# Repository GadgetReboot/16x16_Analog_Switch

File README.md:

# I2C Controlled 16x16_Analog_Switch
<br><br><BR><BR>
MT8816 based 16x16 Analog Switch Matrix

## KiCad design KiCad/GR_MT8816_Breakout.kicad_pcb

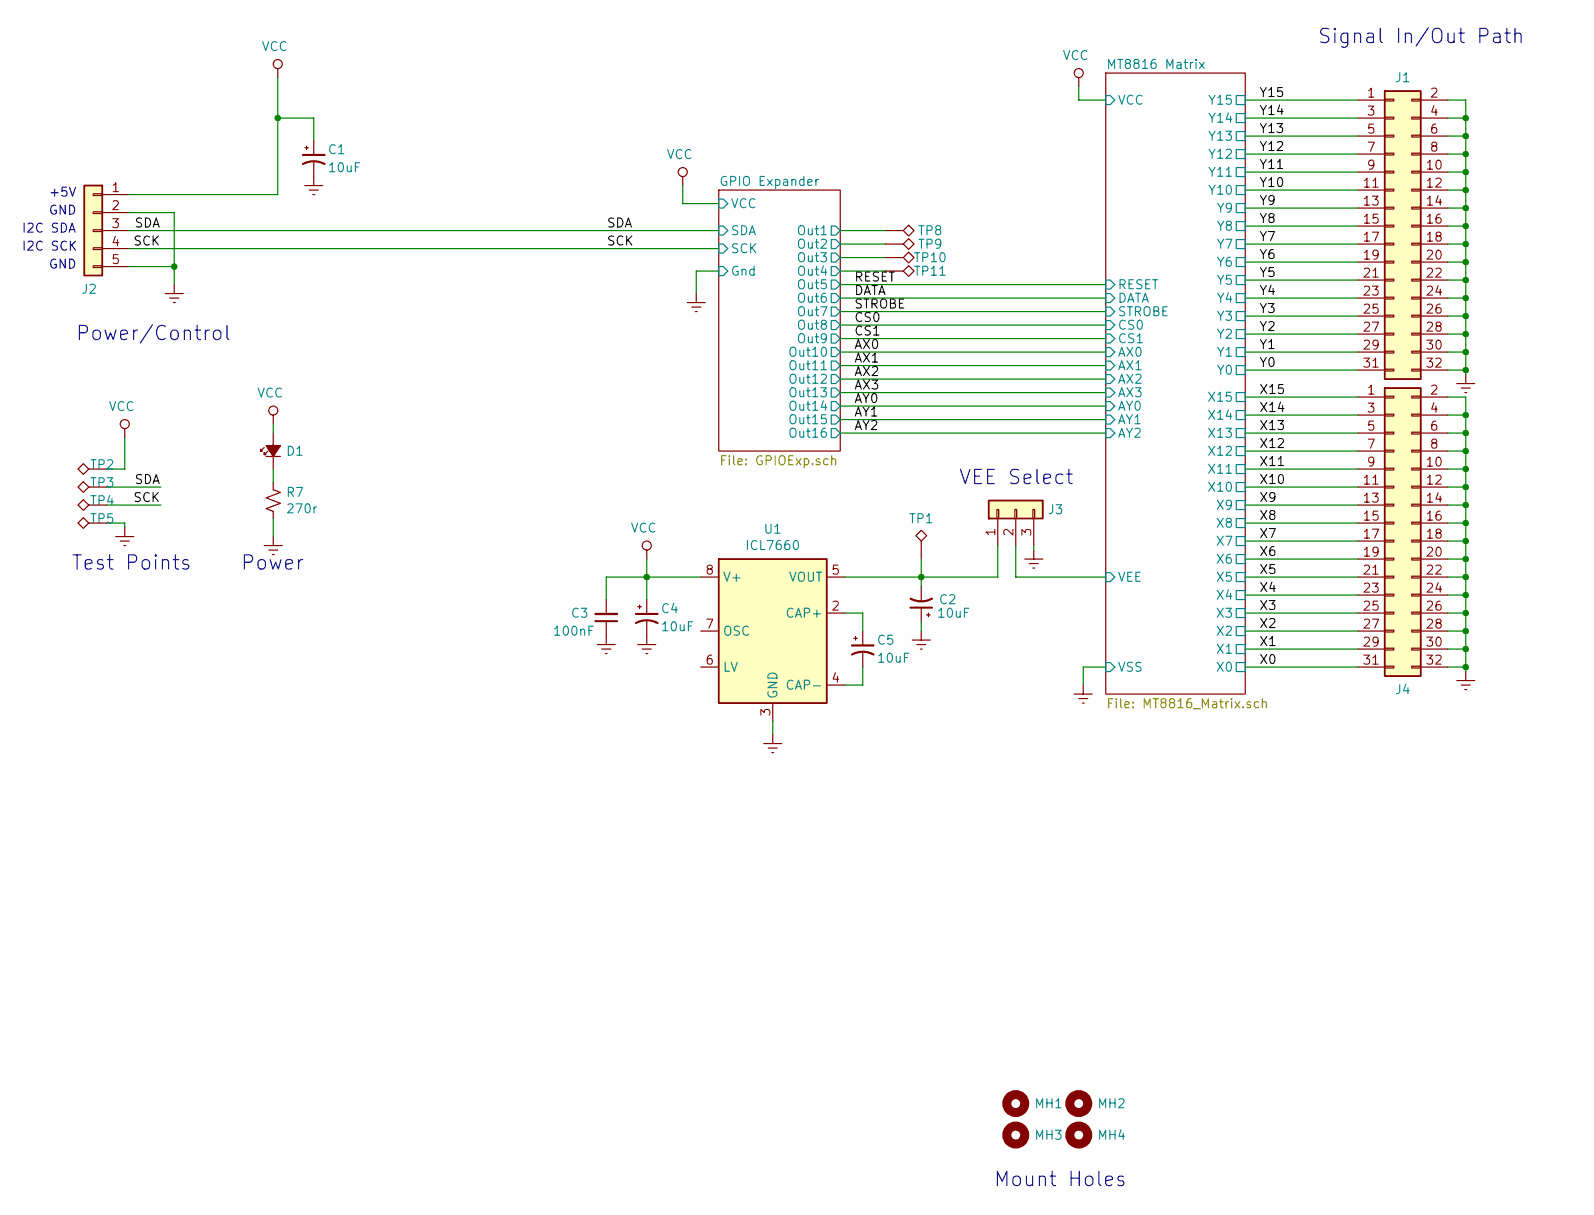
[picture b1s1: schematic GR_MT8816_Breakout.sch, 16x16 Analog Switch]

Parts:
C1, C2, C4, C5: 10uF; CP_Radial_D5.0mm_P2.50mm
C3: 100nF; C_Disc_D3.8mm_W2.6mm_P2.50mm
D1: LED_Small_ALT; LED_D5.0mm
J1, J4: Conn_02x16_Odd_Even; PinHeader_2x16_P2.54mm_Vertical
J2: Conn_01x05; PinHeader_1x05_P2.54mm_Vertical
J3: Conn_01x03; PinHeader_1x03_P2.54mm_Vertical
MH1, MH2, MH3, MH4: MountingHole; MountingHole_3.2mm_M3
R7: 270r; R_Axial_DIN0207_L6.3mm_D2.5mm_P7.62mm_Horizontal
TP1, TP2, TP3, TP4, TP5, TP8, TP9, TP10, TP11: TestPoint_Alt; TestPoint_THTPad_D2.0mm_Drill1.0mm
U1: ICL7660; DIP-8_W7.62mm_Socket_LongPads

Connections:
/GPIO Expander/Out1: TP8.1; also elsewhere on the board
/GPIO Expander/Out2: TP9.1; also elsewhere on the board
/GPIO Expander/Out3: TP10.1; also elsewhere on the board
/GPIO Expander/Out4: TP11.1; also elsewhere on the board
/SCK: J2.4, TP4.1; also elsewhere on the board
/SDA: J2.3, TP3.1; also elsewhere on the board
/X0: J4.31; also elsewhere on the board
/X1: J4.29; also elsewhere on the board
/X2: J4.27; also elsewhere on the board
/X3: J4.25; also elsewhere on the board
/X4: J4.23; also elsewhere on the board
/X5: J4.21; also elsewhere on the board
/X6: J4.19; also elsewhere on the board
/X7: J4.17; also elsewhere on the board
/X8: J4.15; also elsewhere on the board
/X9: J4.13; also elsewhere on the board
/X10: J4.11; also elsewhere on the board
/X11: J4.9; also elsewhere on the board
/X12: J4.7; also elsewhere on the board
/X13: J4.5; also elsewhere on the board
/X14: J4.3; also elsewhere on the board
/X15: J4.1; also elsewhere on the board
/Y0: J1.31; also elsewhere on the board
/Y1: J1.29; also elsewhere on the board
/Y2: J1.27; also elsewhere on the board
/Y3: J1.25; also elsewhere on the board
/Y4: J1.23; also elsewhere on the board
/Y5: J1.21; also elsewhere on the board
/Y6: J1.19; also elsewhere on the board
/Y7: J1.17; also elsewhere on the board
/Y8: J1.15; also elsewhere on the board
/Y9: J1.13; also elsewhere on the board
/Y10: J1.11; also elsewhere on the board
/Y11: J1.9; also elsewhere on the board
/Y12: J1.7; also elsewhere on the board
/Y13: J1.5; also elsewhere on the board
/Y14: J1.3; also elsewhere on the board
/Y15: J1.1; also elsewhere on the board
GNDREF: C1.2, C2.1, C3.1, C4.2, J1.2, J1.4, J1.6, J1.8, J1.10, J1.12, J1.14, J1.16, J1.18, J1.20, J1.22, J1.24, J1.26, J1.28, J1.30, J1.32, J2.2, J2.5, J3.3, J4.2, J4.4, J4.6, J4.8, J4.10, J4.12, J4.14, J4.16, J4.18, J4.20, J4.22, J4.24, J4.26, J4.28, J4.30, J4.32, R7.2, TP5.1, U1.3 (GND); also elsewhere on the board
unnamed: C2.2, J3.1, TP1.1, U1.5 (VOUT)
unnamed: C5.1, U1.2 (CAP+)
unnamed: C5.2, U1.4 (CAP-)
unnamed: D1.1 (K), R7.1
VCC: C1.1, C3.2, C4.1, D1.2 (A), J2.1, TP2.1, U1.8 (V+); also elsewhere on the board
VEE: J3.2; also elsewhere on the board

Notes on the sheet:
Power/Control
Mount Holes
+5V
I2C SDA
I2C SCK
GND
Test Points
Signal In/Out Path
VEE Select
Power

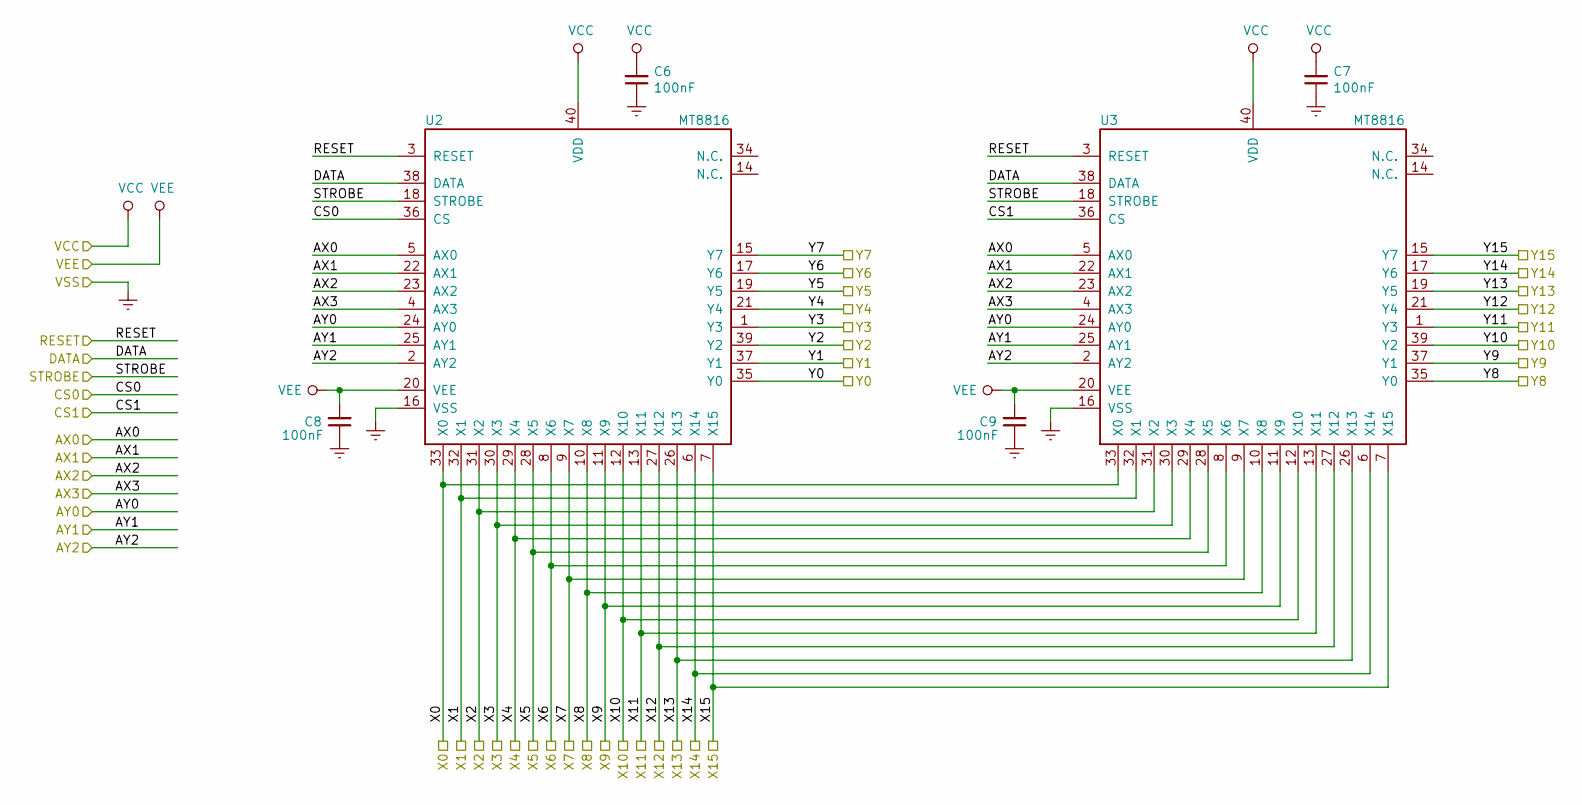
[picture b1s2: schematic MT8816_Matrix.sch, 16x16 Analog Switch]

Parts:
C6, C7, C8, C9: 100nF; C_Disc_D3.8mm_W2.6mm_P2.50mm
U2, U3: MT8816; DIP-40_W15.24mm_Socket_LongPads

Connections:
/AX0: U2.5 (AX0), U3.5 (AX0); also elsewhere on the board
/AX1: U2.22 (AX1), U3.22 (AX1); also elsewhere on the board
/AX2: U2.23 (AX2), U3.23 (AX2); also elsewhere on the board
/AX3: U2.4 (AX3), U3.4 (AX3); also elsewhere on the board
/AY0: U2.24 (AY0), U3.24 (AY0); also elsewhere on the board
/AY1: U2.25 (AY1), U3.25 (AY1); also elsewhere on the board
/AY2: U2.2 (AY2), U3.2 (AY2); also elsewhere on the board
/CS0: U2.36 (CS); also elsewhere on the board
/CS1: U3.36 (CS); also elsewhere on the board
/DATA: U2.38 (DATA), U3.38 (DATA); also elsewhere on the board
/RESET: U2.3 (RESET), U3.3 (RESET); also elsewhere on the board
/STROBE: U2.18 (STROBE), U3.18 (STROBE); also elsewhere on the board
/X0: U2.33 (X0), U3.33 (X0); also elsewhere on the board
/X1: U2.32 (X1), U3.32 (X1); also elsewhere on the board
/X2: U2.31 (X2), U3.31 (X2); also elsewhere on the board
/X3: U2.30 (X3), U3.30 (X3); also elsewhere on the board
/X4: U2.29 (X4), U3.29 (X4); also elsewhere on the board
/X5: U2.28 (X5), U3.28 (X5); also elsewhere on the board
/X6: U2.8 (X6), U3.8 (X6); also elsewhere on the board
/X7: U2.9 (X7), U3.9 (X7); also elsewhere on the board
/X8: U2.10 (X8), U3.10 (X8); also elsewhere on the board
/X9: U2.11 (X9), U3.11 (X9); also elsewhere on the board
/X10: U2.12 (X10), U3.12 (X10); also elsewhere on the board
/X11: U2.13 (X11), U3.13 (X11); also elsewhere on the board
/X12: U2.27 (X12), U3.27 (X12); also elsewhere on the board
/X13: U2.26 (X13), U3.26 (X13); also elsewhere on the board
/X14: U2.6 (X14), U3.6 (X14); also elsewhere on the board
/X15: U2.7 (X15), U3.7 (X15); also elsewhere on the board
/Y0: U2.35 (Y0); also elsewhere on the board
/Y1: U2.37 (Y1); also elsewhere on the board
/Y2: U2.39 (Y2); also elsewhere on the board
/Y3: U2.1 (Y3); also elsewhere on the board
/Y4: U2.21 (Y4); also elsewhere on the board
/Y5: U2.19 (Y5); also elsewhere on the board
/Y6: U2.17 (Y6); also elsewhere on the board
/Y7: U2.15 (Y7); also elsewhere on the board
/Y8: U3.35 (Y0); also elsewhere on the board
/Y9: U3.37 (Y1); also elsewhere on the board
/Y10: U3.39 (Y2); also elsewhere on the board
/Y11: U3.1 (Y3); also elsewhere on the board
/Y12: U3.21 (Y4); also elsewhere on the board
/Y13: U3.19 (Y5); also elsewhere on the board
/Y14: U3.17 (Y6); also elsewhere on the board
/Y15: U3.15 (Y7); also elsewhere on the board
GNDREF: C6.1, C7.1, C8.1, C9.1, U2.16 (VSS), U3.16 (VSS); also elsewhere on the board
VCC: C6.2, C7.2, U2.40 (VDD), U3.40 (VDD); also elsewhere on the board
VEE: C8.2, C9.2, U2.20 (VEE), U3.20 (VEE); also elsewhere on the board

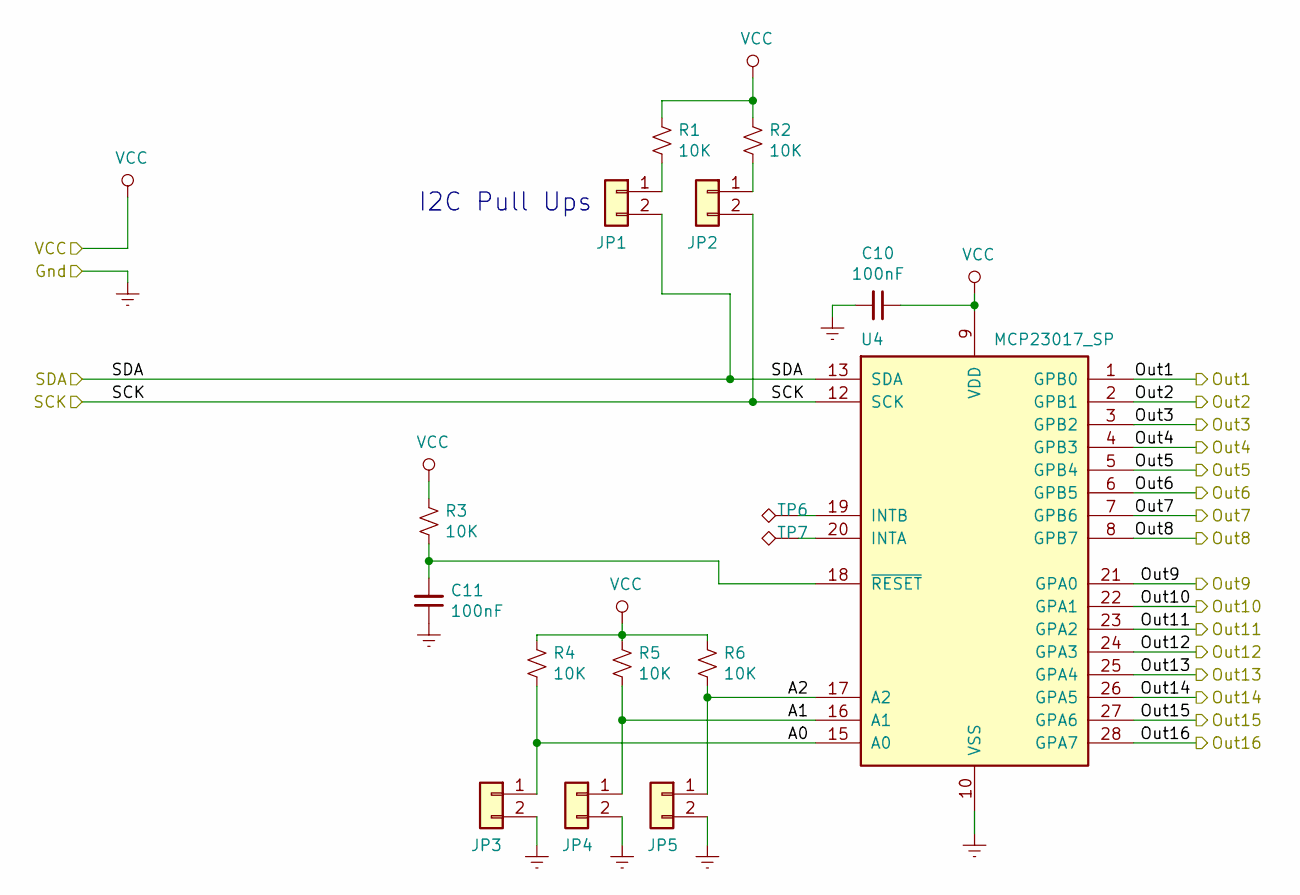
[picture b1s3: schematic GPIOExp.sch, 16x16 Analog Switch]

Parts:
C10, C11: 100nF; C_Disc_D3.8mm_W2.6mm_P2.50mm
JP1, JP2, JP3, JP4, JP5: Conn_01x02; PinHeader_1x02_P2.54mm_Vertical
R1, R2, R3, R4, R5, R6: 10K; R_Axial_DIN0207_L6.3mm_D2.5mm_P7.62mm_Horizontal
TP6, TP7: TestPoint_Alt; TestPoint_THTPad_D2.0mm_Drill1.0mm
U4: MCP23017_SP; DIP-28_W7.62mm

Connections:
/AX0: U4.22 (GPA1); also elsewhere on the board
/AX1: U4.23 (GPA2); also elsewhere on the board
/AX2: U4.24 (GPA3); also elsewhere on the board
/AX3: U4.25 (GPA4); also elsewhere on the board
/AY0: U4.26 (GPA5); also elsewhere on the board
/AY1: U4.27 (GPA6); also elsewhere on the board
/AY2: U4.28 (GPA7); also elsewhere on the board
/CS0: U4.8 (GPB7); also elsewhere on the board
/CS1: U4.21 (GPA0); also elsewhere on the board
/DATA: U4.6 (GPB5); also elsewhere on the board
/GPIO Expander/A0: JP3.1, R4.2, U4.15 (A0)
/GPIO Expander/A1: JP4.1, R5.2, U4.16 (A1)
/GPIO Expander/A2: JP5.1, R6.2, U4.17 (A2)
/GPIO Expander/Out1: U4.1 (GPB0); also elsewhere on the board
/GPIO Expander/Out2: U4.2 (GPB1); also elsewhere on the board
/GPIO Expander/Out3: U4.3 (GPB2); also elsewhere on the board
/GPIO Expander/Out4: U4.4 (GPB3); also elsewhere on the board
/RESET: U4.5 (GPB4); also elsewhere on the board
/SCK: JP2.2, U4.12 (SCK); also elsewhere on the board
/SDA: JP1.2, U4.13 (SDA); also elsewhere on the board
/STROBE: U4.7 (GPB6); also elsewhere on the board
GNDREF: C10.2, C11.1, JP3.2, JP4.2, JP5.2, U4.10 (VSS); also elsewhere on the board
unnamed: C11.2, R3.2, U4.18 (~RESET~)
unnamed: JP1.1, R1.2
unnamed: JP2.1, R2.2
unnamed: TP6.1, U4.19 (INTB)
unnamed: TP7.1, U4.20 (INTA)
VCC: C10.1, R1.1, R2.1, R3.1, R4.1, R5.1, R6.1, U4.9 (VDD); also elsewhere on the board

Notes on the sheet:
I2C Pull Ups

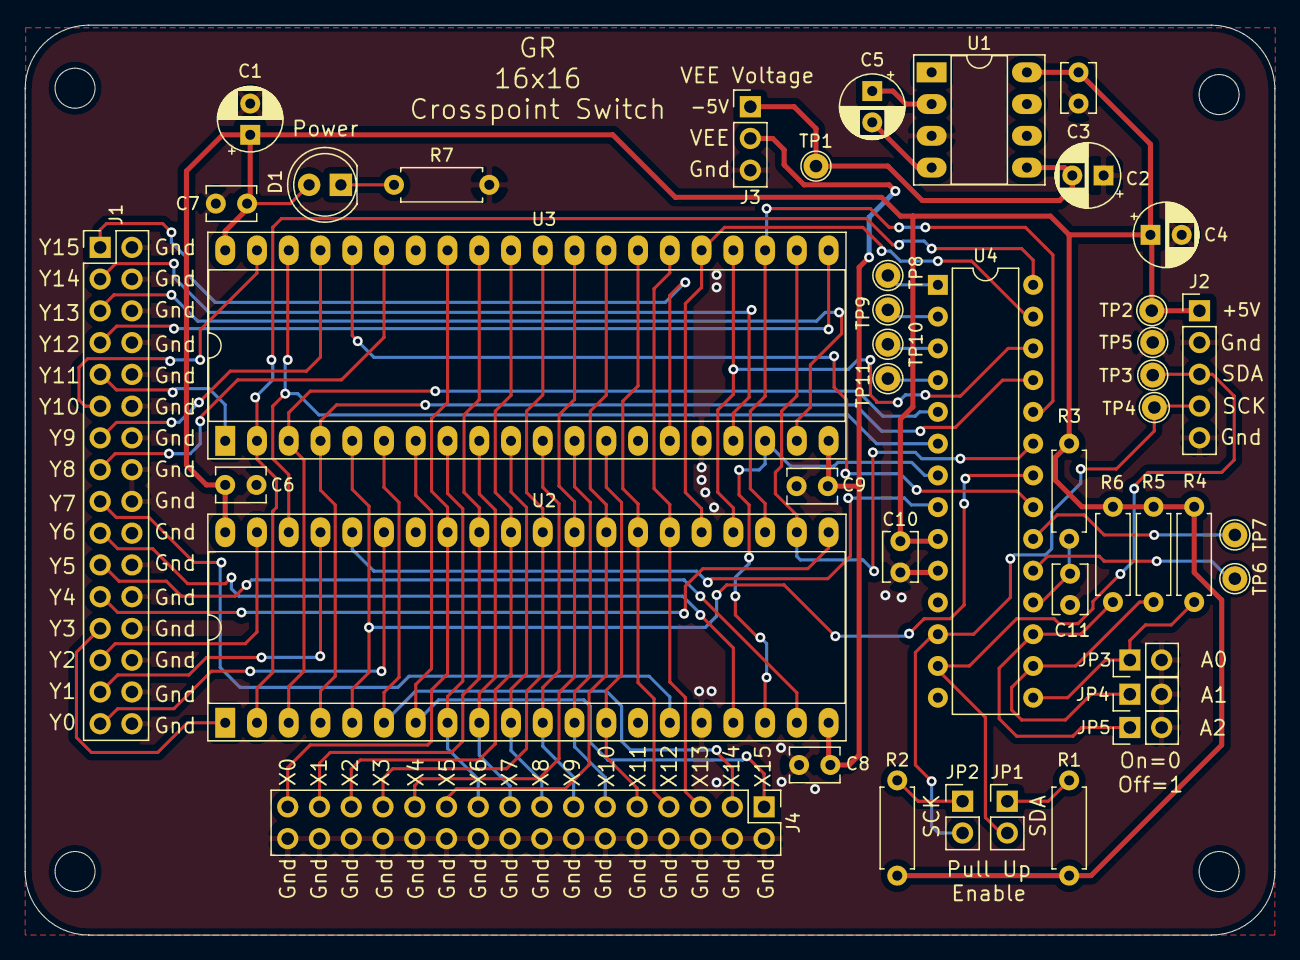
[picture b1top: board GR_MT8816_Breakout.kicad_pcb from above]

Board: 2 copper layers, 99.9 x 72.8 mm, 47 parts (0 on the bottom side), 65 nets.
